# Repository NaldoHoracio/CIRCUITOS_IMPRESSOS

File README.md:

# CIRCUITOS IMPRESSOS

- Exercícios Kicad
- Projeto

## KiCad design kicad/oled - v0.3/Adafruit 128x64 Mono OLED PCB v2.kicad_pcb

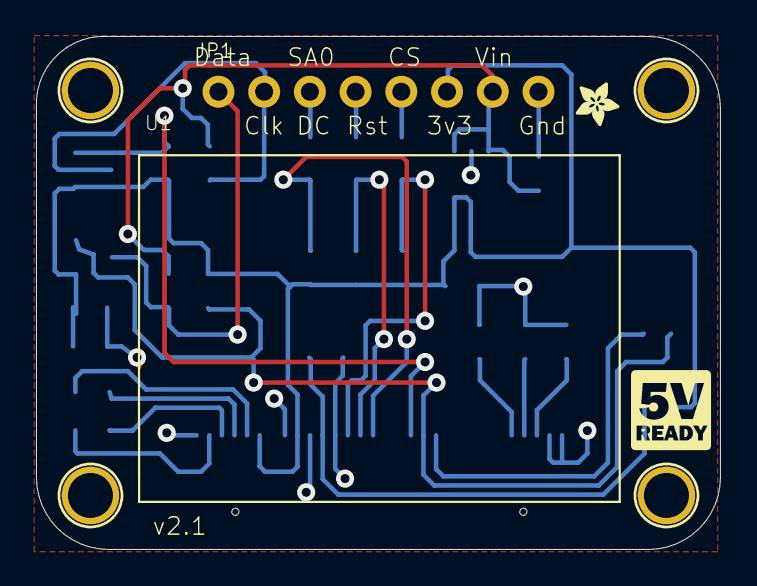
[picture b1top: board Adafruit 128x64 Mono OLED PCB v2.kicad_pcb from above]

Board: 2 copper layers, 38.0 x 28.5 mm, 36 parts (0 on the bottom side), 22 nets.

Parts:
C1, C2, C5: 10uF; 0805
C3, C4, C6, C7: 1uF; 0805
C8: 2.2uF/16V; 0805
D1, D2, D3: 1N4148; SOD-323
FID1, FID2: FIDUCIAL; FIDUCIAL_1MM
JP1: HEADER-1X870MIL; 1X08_ROUND_70
Q1, Q2: BSS138; SOT23-WIDE
R2, R4, R5, R6, R11, R12, R13, R14: 10K; 0805
R3: 390K; 0805
SJ1, SJ2: SOLDERJUMPERREFLOW_NOPASTE; SOLDERJUMPER_REFLOW_NOPASTE
U1: UG-2864HSWEG01; UG-2864HSWEG01_0.96IN_WRAPAROUND
U2: VREG_SOT23-5; SOT23-5
U$3: ADAFRUIT_5MM
U$23, U$24, U$25, U$26: MOUNTINGHOLE2.5; MOUNTINGHOLE_2.5_PLATED
U$27: ADAFRUIT_2.5MM
U$28: LOGIC_5VREADY_5MM

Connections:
3.3V: C2.1, C6.2, C7.2, JP1.6, Q1.1, Q2.1, R4.2, R5.2, R6.2, R11.2, R12.2, SJ2.1, U1.6, U1.9, U2.5
/CS_3.3V: D1.A, R4.1, U1.13
/CS_5.0V: D1.C, JP1.5
/D0/SCLK/SCK_3.3V: Q2.2, R12.1, U1.18
/D0/SCLK/SCK_5.0V: JP1.2, Q2.3, R14.1
/D1/MOSI/SDA1_3.3V: Q1.2, R11.1, SJ1.1, U1.19
/D1/MOSI/SDA_5.0V: JP1.1, Q1.3, R13.1
/DC/SA0_3.3V: D3.A, R6.1, U1.15
/DC/SA0_5.0V: D3.C, JP1.3
/RST_3.3V: D2.A, R5.1, U1.14
/RST_5.0V: D2.C, JP1.4
GND: C1.2, C2.2, C5.1, C6.1, C7.1, C8.1, JP1.8, R2.1, R3.1, U1.1, U1.8, U1.10, U1.12, U1.29, U1.30, U2.2
unnamed: C3.1, U1.3
unnamed: C3.2, U1.2
unnamed: C4.1, U1.5
unnamed: C4.2, U1.4
unnamed: C5.2, U1.28
unnamed: C8.2, U1.27
unnamed: R2.2, SJ2.2, U1.11
unnamed: R3.2, U1.26
unnamed: SJ1.2, U1.20
VIN: C1.1, JP1.7, R13.2, R14.2, U2.1, U2.3

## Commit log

2019-11-22 Atividade 2 finalizada.
2019-11-22 Teste.
2019-11-22 Atualizando.
2019-11-22 Atividade 2.
2019-12-17 Exercício do Esquemático pronto. Versão 0.3
2019-12-19 Esquemático versão 5 e 6.
2020-01-22 Versão 8 do projeto. nRF square. Finalizar o circuito auxiliar e alocar os periféricos.
2020-01-22 Versão 7 do projeto. nRF no padrão vertical. Modificar os periféricos.
2020-01-22 Versão 8 do projeto. nRF finalizada. Verificar o LCD.
2020-01-23 Conferir configurações dos pinos para construir o PCB.
2020-01-23 Atualizando v0.8
2020-01-23 Adicionando footprints.
2020-01-24 Atualizando periféricos. Escolhendo footprints.
